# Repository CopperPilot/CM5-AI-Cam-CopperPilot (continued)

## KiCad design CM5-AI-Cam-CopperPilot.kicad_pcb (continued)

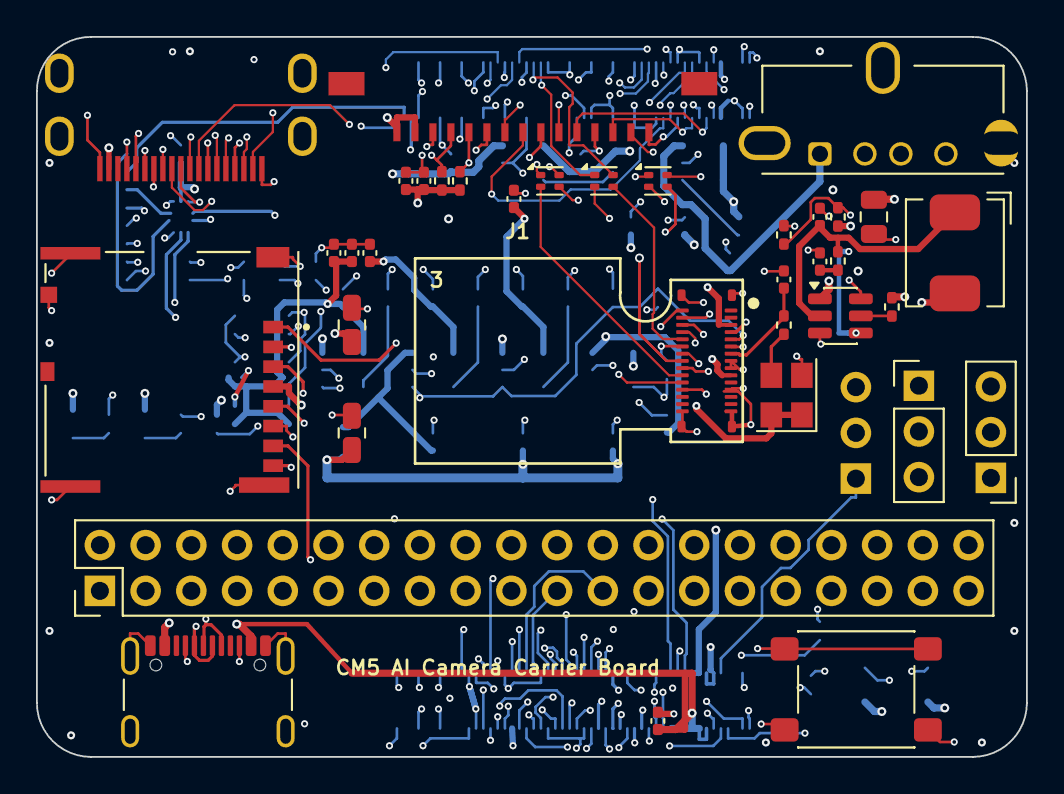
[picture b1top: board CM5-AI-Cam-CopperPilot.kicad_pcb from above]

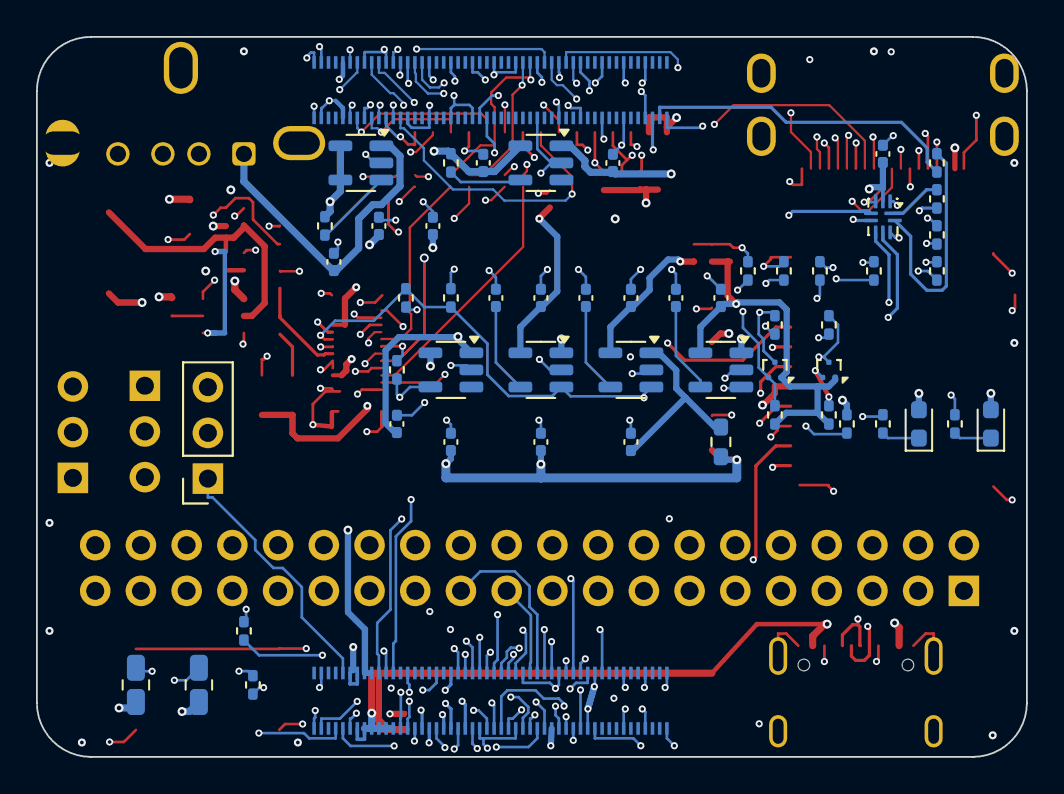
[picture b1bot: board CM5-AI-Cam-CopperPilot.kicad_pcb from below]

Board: 6 copper layers, 55.0 x 40.0 mm, 90 parts (54 on the bottom side), 118 nets.

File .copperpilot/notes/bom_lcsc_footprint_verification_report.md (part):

# Comprehensive BOM, LCSC Sourcing, and Footprint Verification Report

**Project:** CM5 AI Camera Carrier Board (`CM5-AI-Cam-CopperPilot`)  
**Target Assembler:** JLCPCB PCBA / SMT Assembly  
**Audited Artifacts:**
- BOM: `jlcpcb_production/assembly/bom_jlcpcb.csv` (42 lines, 81 placed instances)
- CPL: `jlcpcb_production/assembly/cpl_jlcpcb.csv` (81 placed instances)
- Schematic: `CM5-AI-Cam-CopperPilot.kicad_sch` (91 non-power symbol instances)
- PCB: `CM5-AI-Cam-CopperPilot.kicad_pcb` (90 placed footprint instances)
- Footprint Library: `./CM5.pretty/` (63 footprint definitions)

---

## 1. Fatal Footprint Package Mismatches

Four critical components have fatal mechanical or land pattern incompatibilities between the physical component, the BOM part number, and the placed PCB footprint:

### 1.1 U5: MP1658GTF-Z (Buck Converter)
- **Schematic Reference / Value:** `U5`, `MP1658GTF-Z` (LCSC `C9900009837`)
- **Assigned PCB Footprint:** `CM5:TSOT-23-6`
- **Datasheet Reality:** Monolithic Power Systems (MPS) package code `GTF` is strictly **SOT-563** (1.60 × 1.20 mm body, 1.60 × 1.60 mm total footprint with leads, 0.50 mm lead pitch).
- **Physical Comparison:**
  | Dimension | MP1658GTF-Z (SOT-563) | Placed Footprint (TSOT-23-6) | Conflict Severity |
  |:---|:---|:---|:---|
  | **Lead Pitch** | 0.50 mm | 0.95 mm | **+90% pitch error** |
  | **Pad Center Span (X)** | 1.425 mm | 2.275 mm | **+0.85 mm excessive span** |
  | **Pad Dimensions** | 0.675 × 0.35 mm | 1.325 × 0.60 mm | **Massive oversize** |
- **Assembly Consequence:** The physical SOT-563 IC leads fall entirely into the central dead space between the TSOT-23-6 pads. The component cannot bridge the pads, making automated SMT or hand soldering impossible.
- **Remediation:** Replace footprint with `CM5:SOT-563` (already existing in `./CM5.pretty/SOT-563.kicad_mod`).

### 1.2 Q1, Q2: DMG1012T-7 (I2C Level-Shifter MOSFETs)
- **Schematic Reference / Value:** `Q1, Q2`, `DMG1012T` (LCSC `C20512`)
- **Assigned PCB Footprint:** `CM5:Texas_DRT-3`
- **Datasheet Reality:** Diodes Inc `DMG1012T-7` is packaged strictly in **SOT-523** (body 1.60 × 0.80 mm, overall span 1.60 mm, lead pitch 1.00 mm). The suffix `T` in Diodes Inc parts designates SOT-523.
- **Physical Comparison:**
  | Dimension | DMG1012T-7 (SOT-523) | Placed Footprint (Texas_DRT-3) | Conflict Severity |
  |:---|:---|:---|:---|
  | **Lead Pitch (P1-P2)** | 1.00 mm | 0.70 mm | **+43% pitch error** |
  | **Pad Span (Y)** | 1.29 mm | 0.85 mm | **+0.44 mm mismatch** |
  | **Pad Dimensions** | 0.51 × 0.40 mm | 0.30 × 0.30 mm | **Pads ~50% undersized** |
  | **Component Body** | 1.60 × 1.60 mm | 1.00 × 0.80 mm | **Part 1.6× larger than footprint** |
- **Assembly Consequence:** The physical SOT-523 transistor is ~160% the size of the Texas_DRT-3 land pattern. Solder paste will bridge across the minute 0.3 mm pads, or the transistor pins will hang outside the pads with zero solder fillet.
- **Remediation:** Replace footprint with `CM5:SOT-523` (already existing in `./CM5.pretty/SOT-523.kicad_mod`).

### 1.3 J2: USB-A Host Connector (Vertical vs Right-Angle)
- **Schematic Reference / Value:** `J2`, `USB_A_Vertical`
- **Assigned PCB Footprint:** `CM5:MOLEX_USB_67298-4090` (Vertical through-hole, Molex 105057-0001 equivalent)
- **Assigned BOM Part:** `C720523` -> **XUNPU USB-226-BRY**
- **Datasheet Reality:** XUNPU USB-226-BRY is a **Right-Angle (side-insertion)** through-hole USB-A receptacle. The PCB footprint is a **Vertical (top-insertion)** through-hole receptacle.
- **Physical Comparison:**
  | Feature | BOM Part (XUNPU USB-226-BRY) | PCB Footprint (MOLEX 67298-4090) |
  |:---|:---|:---|
  | **Insertion Axis** | Horizontal (Right-Angle) | Vertical (Straight) |
  | **Signal Pins** | 4 pins bent 90° | 4 straight pins inline at Y=0 (pitch 2.0/2.5 mm) |
  | **Shield Tabs** | 2 lateral side snap-in tabs | 3 triangular retention tabs (X=-3.07, +3.50, +10.07 mm) |
- **Assembly Consequence:** The pins and mechanical retention legs of the right-angle connector cannot mechanically align or insert into the vertical mounting holes on the PCB.
- **Remediation:** Update BOM to a genuine vertical through-hole USB-A connector (e.g. LCSC `C698207` or Molex `105057-0001`), or assign through-hole manual assembly with the correct vertical part.

### 1.4 Module1: Raspberry Pi Compute Module 5 Connector (CPL & BOM Multiplicity Defect)
- **Schematic Reference / Value:** `Module1`, `ComputeModule5-CM5`
- **Assigned PCB Footprint:** `CM5:Raspberry-Pi-5-Compute-Module` (200-pin monolithic footprint)
- **Assigned BOM Part:** `C597931` -> **Hirose DF40C-100DS-0.4V(51)** (Quantity = 1)
- **Datasheet Reality:** The Raspberry Pi CM5 requires **TWO independent 100-pin Hirose DF40 mezzanine connectors** separated by 33.92 mm center-to-center.
- **Assembly Consequence:**
  1. **BOM Shortage:** The BOM lists Quantity 1 of `C597931`, leaving the second 100-pin socket completely unpopulated.
  2. **CPL Centroid Collision:** Because `Module1` is a single monolithic KiCad component, `cpl_jlcpcb.csv` exports a single centroid at (72.8000, -61.4200) on B.Cu. This position corresponds to the dead air gap between the two connectors! An automated pick-and-place machine will attempt to drop a single 100-pin connector into the center void.
- **Remediation:** Split `Module1` into two schematic symbols and footprints (`J1A`, `J1B`) using `CM5:CONN_DF40C-100DS-0.4V51_HIR`. This automatically yields Quantity 2 of `C597931` in the BOM and two accurate placement centroids in the CPL.

---

## 2. BOM LCSC Part Number Verification

Verification of all 42 lines in `jlcpcb_production/assembly/bom_jlcpcb.csv` against component datasheets, pinout, and JLCPCB library:

| Row | Comment / Value | Designators | Qty | Assigned Footprint | LCSC Part # | Manufacturer & MPN | JLCPCB Class | Verification Status & Findings |
|:---:|:---|:---|:---:|:---|:---|:---|:---:|:---|
| 1 | 2.2uF | C1, C12, C5 | 3 | C_0402_1005Metric | C23733 | Samsung CL05A225MP5NRNC | Basic | **VERIFIED MATCH** (2.2uF 10V X5R 0402) |
| 2 | 100nF | C10, C14, C3 | 3 | C_0402_1005Metric | C1525 | Samsung CL05B104KO5NNNC | Basic | **VERIFIED MATCH** (100nF 50V X7R 0402) |
| 3 | 10uF | C11, C22, C4 | 3 | C_0805_2012Metric | C15850 | Samsung CL21A106KAYNNNE | Basic | **VERIFIED MATCH** (10uF 25V X5R 0805) |
| 4 | 1uF | C15, C16, C2, C21, C29, C30, C6, C7, C8, C9 | 10 | C_0402_1005Metric | C52923 | Samsung CL05A105KA5NQNC | Basic | **VERIFIED MATCH** (1uF 25V X5R 0402) |
| 5 | 0.1uF | C17, C18, C23, C24, C27, C28, C31, C32 | 8 | C_0402_1005Metric | C1525 | Samsung CL05B104KO5NNNC | Basic | **VERIFIED MATCH** (0.1uF 50V X7R 0402) |
| 6 | 10pF | C20 | 1 | C_0402_1005Metric | C32949 | Samsung CL05C100JB5NNNC | Basic | **VERIFIED MATCH** (10pF 50V C0G 0402) |
| 7 | 22uF | C25, C26 | 2 | C_0805_2012Metric | C45783 | Samsung CL21A226MAQNNNE | Extended | **VERIFIED MATCH** (22uF 25V X5R 0805) |
| 8 | DSI_15P | DSI1 | 1 | Molex_200528-0150_1x15-1MP_P1.00mm_Horizontal | C2914074 | HDGC 1.0K-FX-15PWB / Molex 200528-0150 | Extended | **VERIFIED MATCH** (15P 1.0mm pitch FPC) |
| 9 | 120R | FB1 | 1 | R_0603_1608Metric | C50843 | Fenghua CBG160808U121T | Basic | **VERIFIED MATCH** (120Ω @ 100MHz 0603 Bead) |
| 10 | Conn_01x03 | H3, H4, H5 | 3 | PinHeader_1x03_P2.54mm_Vertical | C49257 | BOOMELE 2.54-1*3P | Extended | **VERIFIED MATCH** (Requires TH hand assembly) |
| 11 | HDMI_Mini_C | HDMI1 | 1 | HDMI_Mini-C_Molex_47151-0001 | C2013978 | TE Connectivity 2013978-2 / Molex 47151-0001 | Extended | **SOURCING RISK** (Molex 47151-0001 obsolete; C2013978 out of stock) |
| 12 | IMX219_30P | J1 | 1 | Camera_Module_IMX219-D160 | C6539772 | Hirose DF37NB-30DS-0.4V(75) | Extended | **VERIFIED MATCH** (30P 0.4mm pitch mezzanine) |
| 13 | USB_A_Vertical | J2 | 1 | MOLEX_USB_67298-4090 | C720523 | XUNPU USB-226-BRY | Extended | **FATAL MISMATCH** (BOM is Right-Angle; Footprint is Vertical TH) |
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
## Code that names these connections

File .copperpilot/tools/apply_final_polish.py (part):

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        pin_to_net[(ref, str(pin))] = clean

# Power flags
pin_to_net[("#FLG01", "1")] = "CM5_5V"
pin_to_net[("#FLG02", "1")] = "PWR_3V3"
pin_to_net[("#FLG09", "1")] = "GPIO_VREF"
pin_to_net[("#FLG010", "1")] = "CAM_FB1_OUT"
pin_to_net[("#FLG011", "1")] = "GND"
pin_to_net[("#PWR01", "1")] = "GND"

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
